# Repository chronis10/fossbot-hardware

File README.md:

The newer version of the FOSSBot is available here, where you can find the 3D models and instructions to build it.

The redesign of the robot is complete, and the files are available for download.

The circuit schematics, instructions, and firmware code will be available soon.

## 3D Printable Part List
---
* [Battery Cover](stl/batterycover.stl)

---
* [Bottom Base](stl/b1_p_f.stl)

---
* [Middle Base](stl/b2_p_f.stl)

---
* [Top Base](stl/b3_p_f.stl)

---
* [Left eye](stl/left_eye.stl)
* [Right eye](stl/right_eye.stl)

---
* [Top Cover](stl/lego_top.stl)

---
* [Pen Holder](stl/pen_holder.stl)

---
* [Spoiler Left](stl/fender_left.stl)
* [Spoiler Right](stl/fender_right.stl)

---

## PCB
---
* [Main PCB production file](PCB/production/fossbot-v2-main-pcb.zip)

---
* [Battery module production file](PCB/production/battery_module.zip)

---

## Hardware/Software Development Team
* Christos Chronis
* Dimitris Charitos
* Adrien BRACQ - Barbatronic

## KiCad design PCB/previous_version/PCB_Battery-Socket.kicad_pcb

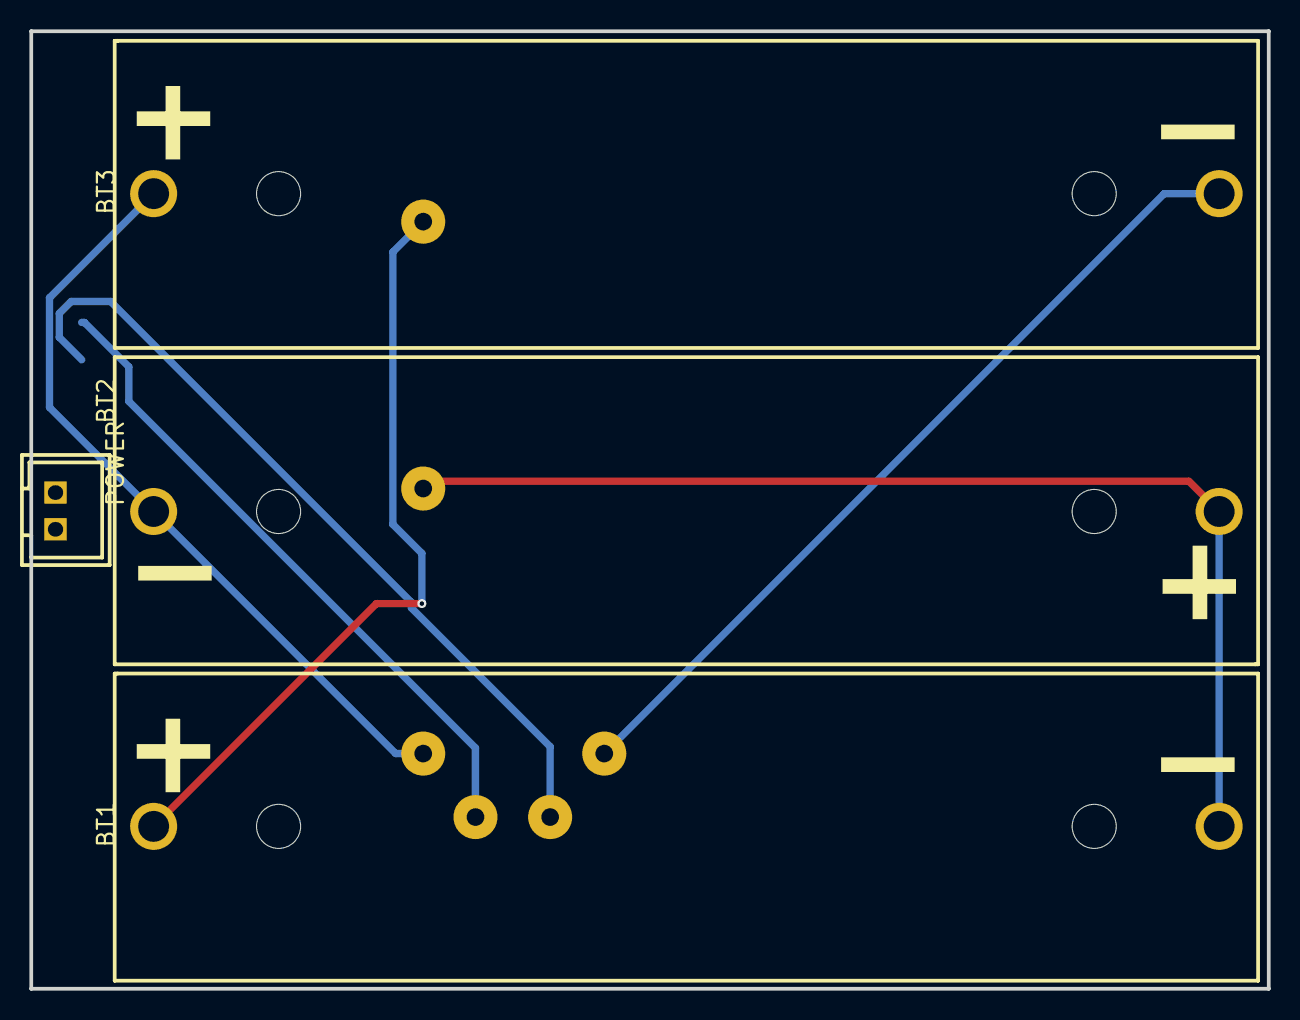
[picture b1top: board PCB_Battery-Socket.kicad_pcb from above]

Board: 2 copper layers, 84.2 x 65.2 mm, 5 parts (0 on the bottom side), 6 nets.

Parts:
BMS1: HX-3S-01
BT1, BT2, BT3: BH-18650-A5BJ001; BAT-TH_18650-A5BJ001
POWER: XH2.54-2PIN-直针; CONN-TH_XH2.54-2P

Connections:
BMS1_5: BMS1.5, POWER.2
BMS1_6: BMS1.6, POWER.1
BT1_1: BMS1.1, BT1.1
BT2_1: BMS1.2, BT1.2, BT2.1
BT3_1: BMS1.3, BT2.2, BT3.1
BT3_2: BMS1.4, BT3.2

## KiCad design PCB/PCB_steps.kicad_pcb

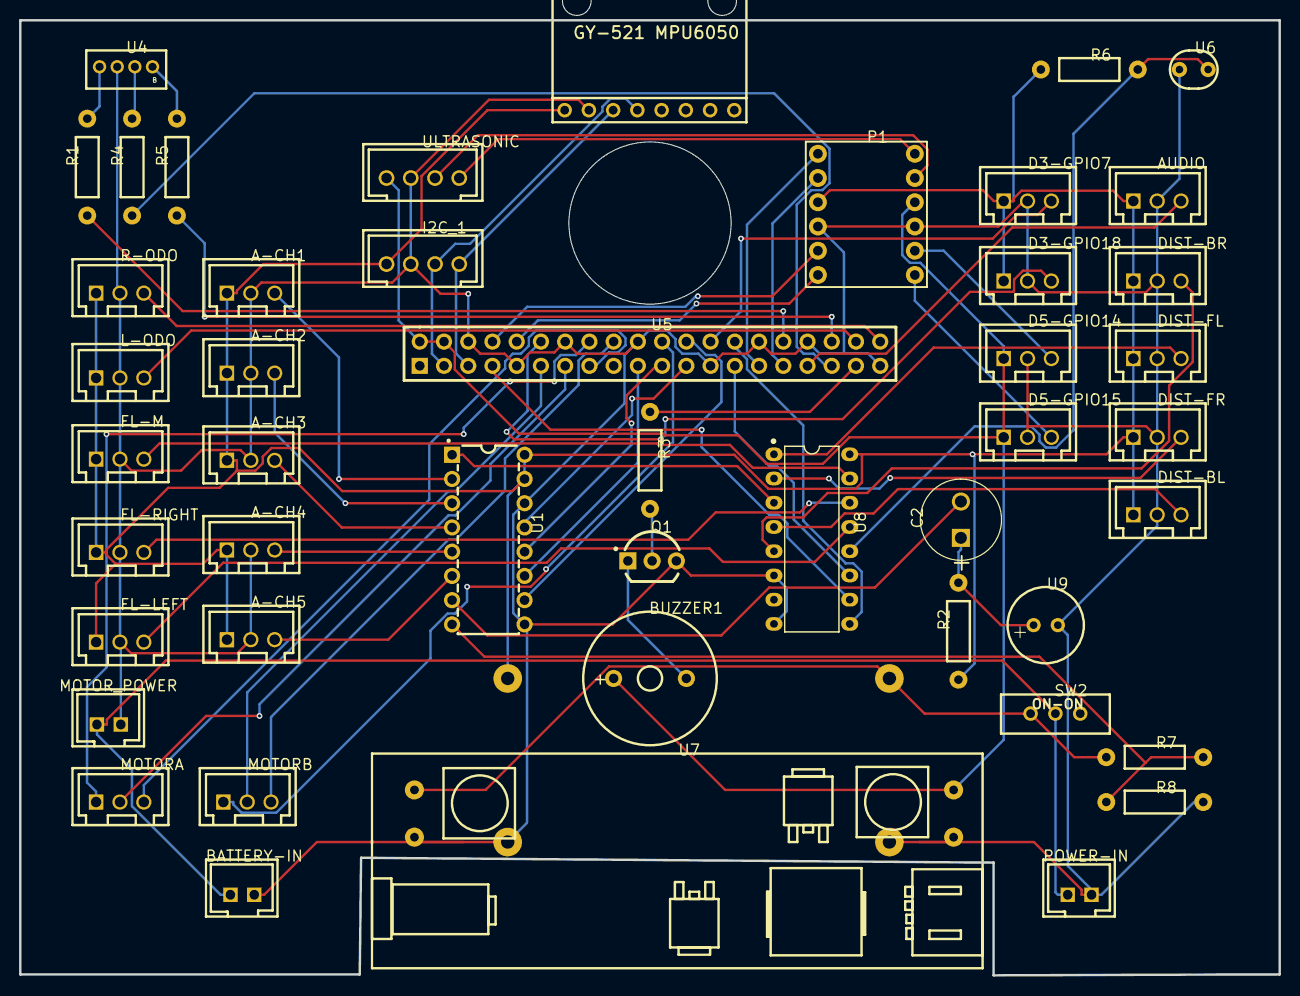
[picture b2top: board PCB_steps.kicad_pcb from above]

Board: 2 copper layers, 132.0 x 100.1 mm, 48 parts (0 on the bottom side), 59 nets.

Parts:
A-CH1, A-CH2, A-CH3, A-CH4, A-CH5: HCZZ0126-3; CONN-TH_3P-P2.50_3PIN
AUDIO: HCZZ0126-3; CONN-TH_3P-P2.50_3PIN
BATTERY-IN: XH2.54-2PIN-直针; CONN-TH_XH2.54-2P
BUZZER1: FSD-1407B-12V; BUZ-TH_BD14.0-P7.60-D0.7-FD
C2: 1µF; ELECTRO-8.6MM
D3-GPIO7, D3-GPIO18, D5-GPIO14, D5-GPIO15: HCZZ0126-3; CONN-TH_3P-P2.50_3PIN
DIST-BL: HCZZ0126-3; CONN-TH_3P-P2.50_3PIN
DIST-BR: HCZZ0126-3; CONN-TH_3P-P2.50_3PIN
DIST-FL: HCZZ0126-3; CONN-TH_3P-P2.50_3PIN
DIST-FR: HCZZ0126-3; CONN-TH_3P-P2.50_3PIN
FL-LEFT: HCZZ0126-3; CONN-TH_3P-P2.50_3PIN
FL-M: HCZZ0126-3; CONN-TH_3P-P2.50_3PIN
FL-RIGHT: HCZZ0126-3; CONN-TH_3P-P2.50_3PIN
I2C_1: HCZZ0126-4; CONN-TH_XH2.54-4P
L-ODO: HCZZ0126-3; CONN-TH_3P-P2.50_3PIN
MOTORA: HCZZ0126-3; CONN-TH_3P-P2.50_3PIN
MOTORB: HCZZ0126-3; CONN-TH_3P-P2.50_3PIN
MOTOR_POWER: XH2.54-2PIN-直针; CONN-TH_XH2.54-2P
P1: Logic_Level Bidirectional; LOGIC_LEVEL BIDIRECTIONAL
POWER-IN: XH2.54-2PIN-直针; CONN-TH_XH2.54-2P
Q1: 2N2222A; TO-92-3 (NPN)_L4.8-W3.7-P2.54-R
R1, R4, R5: 270Ω; AXIAL-0.4
R2: 2.2KΩ; AXIAL-0.4
R3, R8: 1KΩ; AXIAL-0.4
R6: 10KΩ; AXIAL-0.4
R7: 3KΩ; AXIAL-0.4
R-ODO: HCZZ0126-3; CONN-TH_3P-P2.50_3PIN
SW2: 3-Pin SPDT Slide Switch; 3-PIN SPDT SLIDE SWITCH_
U1: MCP3008-I/P; PDIP-16_L19.3-W6.5-P2.54-LS7.6-BL
U2: GY521; GY521 MPU6050
U3: DC-DC LM2596S; DC-DC LM2596S-ADJ
U4: RGB_LED_Common_Cathod; RGB-LED-TH-COMMON-CATHODE
U5: Raspberry PI 4 (HEADER 44PINS); RASPBERRY PI 4 2*40 PIN FEMALE
U6: LDR; LDR (LDRSC058S)
U7: HCW-P715
U8: TC74HC4051APF; PDIP-16_L19.3-W6.4-P2.54-LS7.94-BL
U9: MicroPhone; MICROPHONE
ULTRASONIC: HCZZ0126-4; CONN-TH_XH2.54-4P

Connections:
CH0: U1.1, U8.3
CH6: C2.-, U1.7
CH7: R7.2, R8.1, U1.8
CLK: U1.13, U5.23
CS: U1.10, U5.24
DIN: U1.11, U5.19
DIST-BL_3: DIST-BL.3, U8.4
DIST-BR_3: DIST-BR.3, U8.5
DIST-FL_3: DIST-FL.3, U8.1
DIST-FR_3: DIST-FR.3, U8.2
DOUT: U1.12, U5.21
FL-LEFT_3: FL-LEFT.3, U8.13
FL-M_3: FL-M.3, U8.15
FL-RIGHT_3: FL-RIGHT.3, U8.14
GND: A-CH1.2, A-CH2.2, A-CH3.2, A-CH4.2, A-CH5.2, AUDIO.2, BATTERY-IN.2, D3-GPIO7.2, D3-GPIO18.2, D5-GPIO14.2, D5-GPIO15.2, DIST-BL.2, DIST-BR.2, DIST-FL.2, DIST-FR.2, FL-LEFT.2, FL-M.2, FL-RIGHT.2, I2C_1.2, L-ODO.2, MOTOR_POWER.2, P1.4, P1.9, POWER-IN.2, Q1.3, R8.2, R-ODO.2, U1.9, U1.14, U2.2, U3.2, U3.3, U4.GND, U5.6, U5.9, U5.14, U5.20, U5.25, U5.30, U5.34, U5.39, U6.1, U7.2, U7.3, U8.6, U8.8, U9.2, ULTRASONIC.2
GPIO0: U5.27, U8.11
GPIO1: U5.28, U8.9
GPIO4: U5.7, U8.10
GPIO5: P1.12, U5.29
GPIO6: P1.11, U5.31
GPIO7: D3-GPIO7.3, U5.26
GPIO12: R1.1, U5.32
GPIO13: AUDIO.3, U5.33
GPIO14: P1.8, U5.8
GPIO15: P1.7, U5.10
GPIO16: R5.1, U5.36
GPIO17: MOTORB.2, U5.11
GPIO18: D3-GPIO18.3, U5.12
GPIO19: R4.1, U5.35
GPIO20: L-ODO.3, U5.38
GPIO21: R-ODO.3, U5.40
GPIO22: MOTORA.3, U5.15
GPIO23: MOTORA.1, U5.16
GPIO24: MOTORB.3, U5.18
GPIO25: MOTORB.1, U5.22
GPIO26: R3.1, U5.37
GPIO27: MOTORA.2, U5.13
LDR: R6.2, U6.2, U8.12
P1_1: P1.1, ULTRASONIC.4
P1_2: P1.2, ULTRASONIC.3
P1_5: D5-GPIO14.3, P1.5
P1_6: D5-GPIO15.3, P1.6
Q1_1: BUZZER1.2, Q1.1
Q1_2: Q1.2, R3.2
R1_2: R1.2, U4.R
R4_2: R4.2, U4.G
R5_2: R5.2, U4.B
SCL: I2C_1.4, U2.3, U5.5
SDA: I2C_1.3, U2.4, U5.3
SW12V: R7.1, SW2.ON_1, U3.4, U7.1
U1_2: A-CH1.3, U1.2
U1_3: A-CH2.3, U1.3
U1_4: A-CH3.3, U1.4
U1_5: A-CH4.3, U1.5
U1_6: A-CH5.3, U1.6
U9_1: C2.+, R2.2, U9.1
VCC: A-CH1.1, A-CH2.1, A-CH3.1, A-CH4.1, A-CH5.1, AUDIO.1, D3-GPIO7.1, D3-GPIO18.1, DIST-BL.1, DIST-BR.1, DIST-FL.1, DIST-FR.1, FL-LEFT.1, FL-M.1, FL-RIGHT.1, I2C_1.1, L-ODO.1, P1.10, R2.1, R6.1, R-ODO.1, U1.15, U1.16, U2.1, U3.1, U8.16
VCC5V: BUZZER1.1, D5-GPIO14.1, D5-GPIO15.1, P1.3, U5.2, U5.4, U7.4, ULTRASONIC.1
VCC12V: BATTERY-IN.1, MOTOR_POWER.1, POWER-IN.1, SW2.GND

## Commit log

2024-02-27 instruction for sensors and hardware diagnostics
2024-04-23 user's manual
2024-06-04 new instructions and schematics
2025-02-21 fosssbot new designs
2025-02-21 fossbot new designs
2025-02-21 Update README with new FOSSBot version details and 3D printable part list
2025-02-24 robot schematics
2025-06-09 Rename PR4 - Instruction manual for the assembly and programming of S.T.E.P.S. educational robot.docx.pdf to PR4 - Instruction manual for the assembly and programming of S.T.E.P.S. educational robot.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
2025-06-09 new instructions
2025-07-02 pcb files for kickad and easyeda
2026-01-26 new designs
2026-01-26 new pcb images
2026-01-26 Update README with PCB production files
    Added PCB production files and images to README.
2026-01-26 Add production instructions to README.md
2026-01-26 production files added
2026-01-26 Add eye STL files and images to README
2026-02-02 fix pcb base
2026-02-04 power override
